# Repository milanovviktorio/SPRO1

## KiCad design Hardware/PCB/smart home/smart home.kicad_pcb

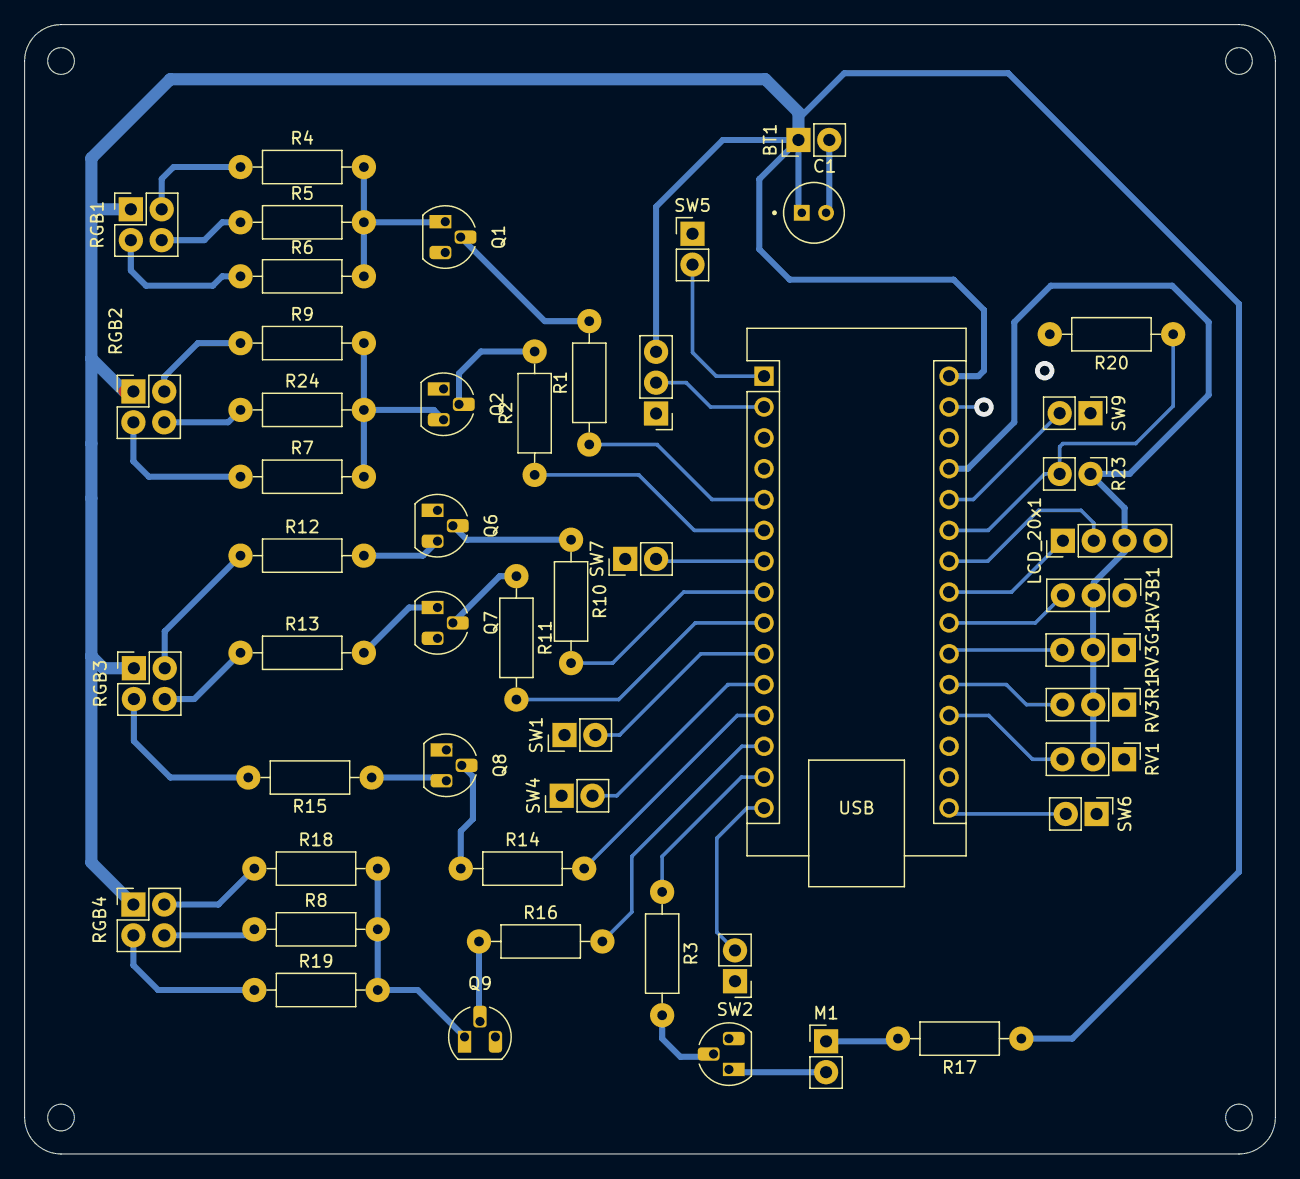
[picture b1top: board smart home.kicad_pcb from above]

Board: 2 copper layers, 103.0 x 93.0 mm, 54 parts (0 on the bottom side), 52 nets.

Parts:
A1: Arduino_Nano_v3.x; Arduino_Nano
BT1: 9V; PinHeader_1x02_P2.54mm_Vertical
C1: 4.7µF; CAPPRD200W45D500H500
H1, H2, H3, H4: MountingHole; MountingHole_2.2mm_M2
HC–SR505PIR1: PinHeader_1x03_P2.54mm_Vertical
LCD_20x1: PinHeader_1x04_P2.54mm_Vertical
M1: Fan; PinHeader_1x02_P2.54mm_Vertical
Q1, Q2, Q6, Q7, Q8, Q9: BC547C; TO-92_HandSolder
Q3: BC547; TO-92_HandSolder
R1, R2, R16: 15k; R_Axial_DIN0207_L6.3mm_D2.5mm_P10.16mm_Horizontal
R3: 7.5k; R_Axial_DIN0207_L6.3mm_D2.5mm_P10.16mm_Horizontal
R4, R7, R12, R18: 360; R_Axial_DIN0207_L6.3mm_D2.5mm_P10.16mm_Horizontal
R5, R6, R8, R9, R13, R15, R19, R24: 300; R_Axial_DIN0207_L6.3mm_D2.5mm_P10.16mm_Horizontal
R10, R11, R14: 45k; R_Axial_DIN0207_L6.3mm_D2.5mm_P10.16mm_Horizontal
R17: 52; R_Axial_DIN0207_L6.3mm_D2.5mm_P10.16mm_Horizontal
R20: 10k; R_Axial_DIN0207_L6.3mm_D2.5mm_P10.16mm_Horizontal
R23: LDR03; PinHeader_1x02_P2.54mm_Vertical
RGB1, RGB2, RGB3, RGB4: FD-5WSRGB-A; PinSocket_2x02_P2.54mm_Vertical
RV1, RV3B1, RV3G1, RV3R1: 10k; PinHeader_1x03_P2.54mm_Vertical
SW1, SW2, SW6, SW9: SW_SPST; PinHeader_1x02_P2.54mm_Vertical
SW4, SW5, SW7: SW_Push; PinHeader_1x02_P2.54mm_Vertical

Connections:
+5V: A1.27 (+5V), LCD_20x1.3 (Vcc), R23.1, RV1.3 (2), RV3B1.3 (2), RV3G1.3 (2), RV3R1.3 (2)
C_button_1: A1.1 (D1/TX), SW5.2
C_button_2: A1.11 (D8), SW4.2
C_button_3: A1.7 (D4), SW7.2
GND: A1.4 (GND), A1.29 (GND), BT1.2 (-), HC–SR505PIR1.1 (GND(-)), LCD_20x1.4 (GND), Q1.3 (E), Q2.1 (C), Q3.3 (E), Q6.1 (C), Q7.3 (E), Q8.1 (C), Q9.3 (E), R20.2, RV1.1, RV3B1.1, RV3G1.1, RV3R1.1, SW1.1 (A), SW2.1 (A), SW4.1, SW5.1, SW6.1 (A), SW7.1, SW9.1 (A)
LDR: A1.25 (A6), R20.1, R23.2
MC_signal: A1.2 (D0/RX), HC–SR505PIR1.2 (Signal_O/P(S))
MD_light_enable: A1.13 (D10), R16.2
unnamed: M1.1 (+), R17.2
unnamed: M1.2 (-), Q3.1 (C)
unnamed: Q1.2 (B), R1.2
unnamed: Q1.1 (C), R4.2, R5.2, R6.2
unnamed: Q2.2 (B), R2.2
unnamed: Q2.2 (E), R7.2, R9.2, R24.2
unnamed: Q3.2 (B), R3.2
unnamed: Q6.2 (B), R10.1
unnamed: Q6.3 (E), R12.2
unnamed: Q7.2 (B), R11.1
unnamed: Q7.1 (C), R13.2
unnamed: Q8.2 (B), R14.1
unnamed: Q8.3 (E), R15.1
unnamed: Q9.2 (B), R16.1
unnamed: Q9.1 (C), R8.2, R18.2, R19.2
unnamed: R6.1, RGB1.2
unnamed: R5.1, RGB1.4
unnamed: R4.1, RGB1.3
unnamed: R9.1, RGB2.3
unnamed: R24.1, RGB2.4
unnamed: R7.1, RGB2.2
unnamed: R15.2, RGB3.2
unnamed: R13.1, RGB3.4
unnamed: R12.1, RGB3.3
unnamed: R19.1, RGB4.2
unnamed: R8.1, RGB4.4
unnamed: R18.1, RGB4.3
R1-D: A1.19 (A0), RV1.2 (3)
R1-enable: A1.6 (D3), R2.1
R2-enable: A1.5 (D2), R1.1
R2_S1: A1.10 (D7), SW1.2 (B)
R2_S2: A1.15 (D12), SW2.2 (B)
R3-B: A1.22 (A3), RV3B1.2 (3)
R3-G: A1.21 (A2), RV3G1.2 (3)
R3-R: A1.20 (A1), RV3R1.2 (3)
R3B enable: A1.12 (D9), R14.2
R3G enable: A1.9 (D6), R11.2
R3R enable: A1.8 (D5), R10.2
R3_S1: A1.26 (A7), SW9.2 (B)
SCL: A1.24 (A5), LCD_20x1.2 (SCL)
SDA: A1.23 (A4), LCD_20x1.1 (SDA)
VCC: A1.30 (VIN), BT1.1 (+), C1.P, HC–SR505PIR1.3 (Possitive_ps), R17.1, RGB1.1, RGB2.1, RGB3.1, RGB4.1
fan enable: A1.14 (D11), R3.1
fan switch: A1.16 (D13), SW6.2 (B)

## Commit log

2024-10-23 Add files via upload
    schematic for now will be cleaned up and updated as we go along(subject so change)
2024-10-23 Added folders
2024-10-26 made the sch into a project
2024-10-27 cleaning up elec scheme + pot + rgb custom models
2024-10-31 PCB should be right about done
2024-11-14 Update resistors and fan circuit
2024-11-16 revision changed
2024-11-21 Software organized and started
2024-11-21 main door working
2024-11-22 Add files via upload
    Maybe not broken
2024-11-22 main door finished
2024-11-22 Add files via upload
    final versiom
2024-11-23 added gerber files
2024-11-24 Unscrew folder structure, add updated gerbers
2024-12-04 fan code
2024-12-04 update kicad proj to current. new pcb, gerber, etc.
2024-12-04 state machine init, library tweaked
2024-12-09 definitions (questionable)
2024-12-12 code-final-ver1
2024-12-13 finalcode-update-dec13
2024-12-15 finalcode-update-dec15
2024-12-16 dec16bugs
2024-12-17 code refactoring
2024-12-17 codefix-dec17
2024-12-18 finalcode
2024-12-29 folder organization
